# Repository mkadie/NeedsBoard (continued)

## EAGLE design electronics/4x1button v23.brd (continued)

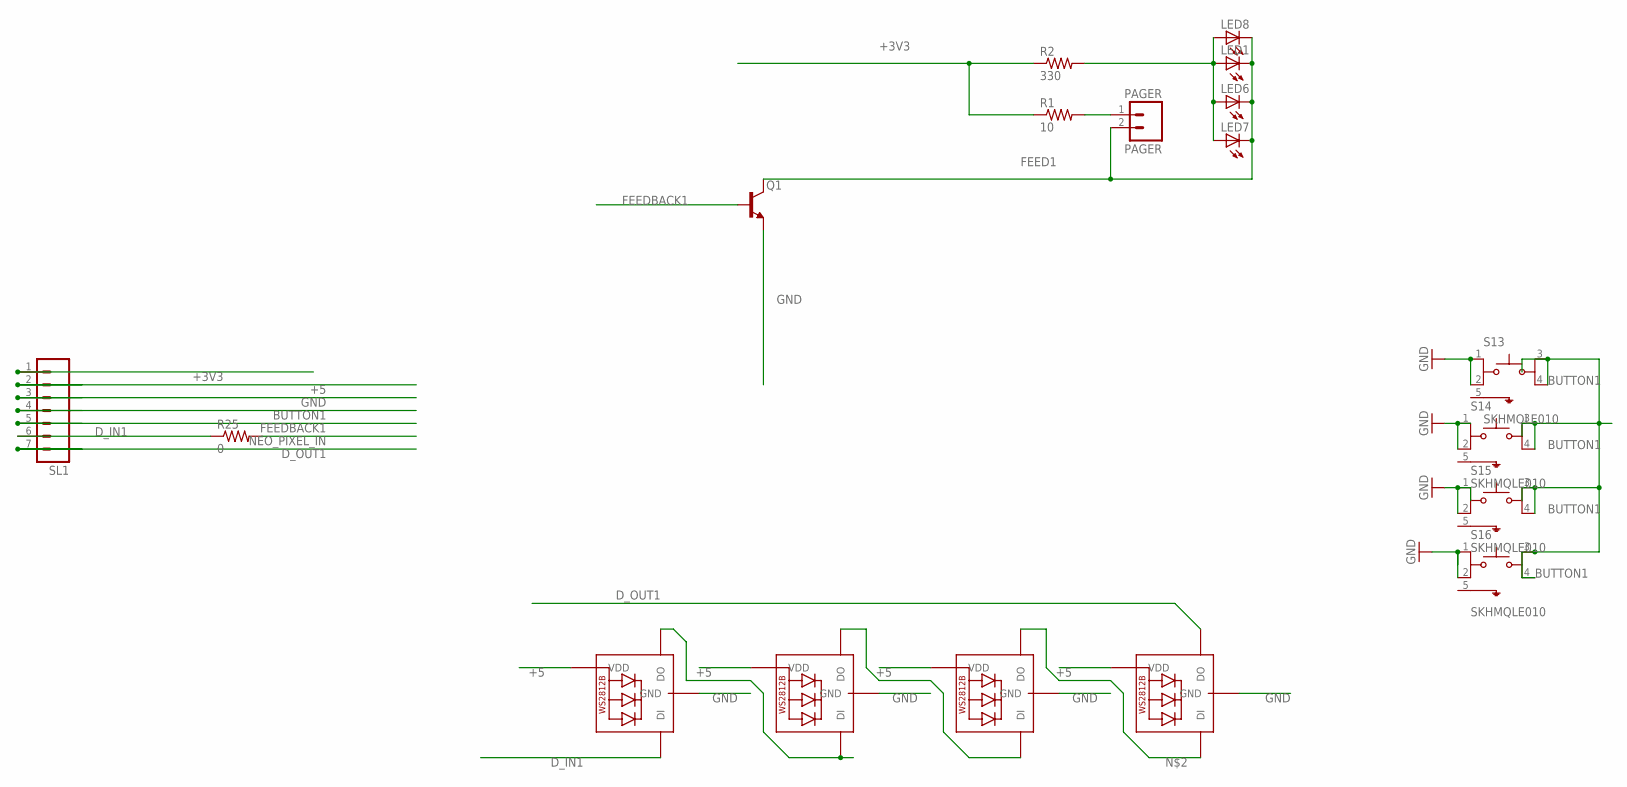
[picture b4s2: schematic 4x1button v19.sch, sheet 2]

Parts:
LED1, LED6, LED7, LED8: LEDCHIP-LED0805; CHIP-LED0805
LED2, LED3, LED4, LED5: WS2812B-V5/W; WS2812B
PAGER: PAGER; 02PA
Q1: MMUN2216; SOT95P237X112-3N
R1: 10; R0805
R2: 330; R0805
R25: 0; R0805
S13, S14, S15, S16: SKHMQLE010; SW_SKHMQLE010
SL1: MA07; 07PA

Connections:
5: S13.5, S14.5, S15.5, S16.5; also elsewhere on the board
+3V3: R1.1, R2.1, SL1.1; also elsewhere on the board
+5: LED2.1-VDD (VDD), LED3.1-VDD (VDD), LED4.1-VDD (VDD), LED5.1-VDD (VDD), SL1.2; also elsewhere on the board
BUTTON1: S13.3, S13.4, S14.3, S14.4, S15.3, S15.4, S16.3, S16.4, SL1.4; also elsewhere on the board
D_IN1: LED2.4-DIN (DI), R25.1, SL1.6
D_OUT1: LED5.2-DOUT (DO), SL1.7; also elsewhere on the board
FEED1: LED1.C, LED6.C, LED7.C, LED8.C, PAGER.2, Q1.3 (C)
FEEDBACK1: Q1.1 (B), SL1.5; also elsewhere on the board
GND: LED2.3-GND (GND), LED3.3-GND (GND), LED4.3-GND (GND), LED5.3-GND (GND), Q1.2 (E), S13.1, S13.2, S14.1, S14.2, S15.1, S15.2, S16.1, S16.2, SL1.3; also elsewhere on the board
unnamed: PAGER.1, R1.2
unnamed: LED4.2-DOUT (DO), LED5.4-DIN (DI)
unnamed: LED1.A, LED6.A, LED7.A, LED8.A, R2.2
unnamed: LED2.2-DOUT (DO), LED3.4-DIN (DI)
unnamed: LED3.2-DOUT (DO), LED4.4-DIN (DI)
NEO_PIXEL_IN: R25.2; also elsewhere on the board

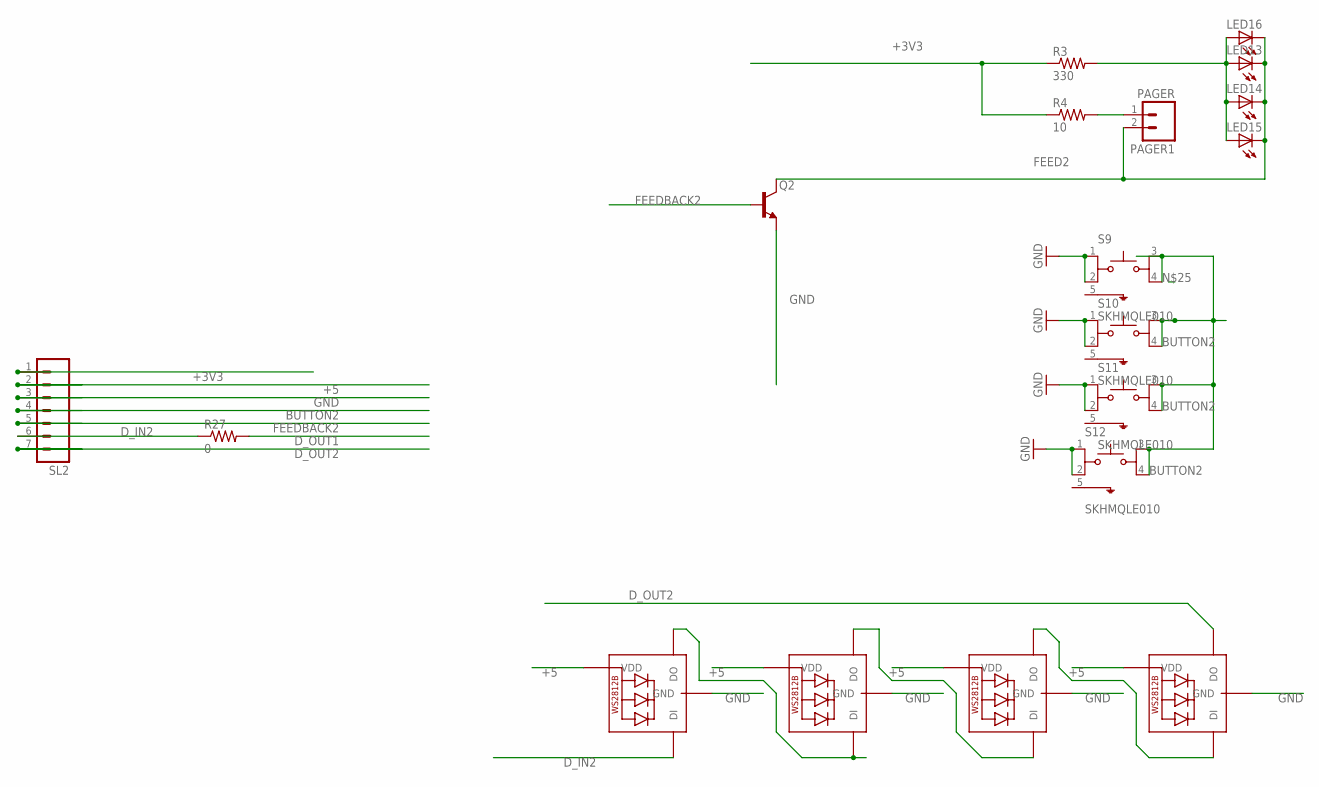
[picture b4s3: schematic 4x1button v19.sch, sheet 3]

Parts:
LED9, LED10, LED11, LED12: WS2812B-V5/W; WS2812B
LED13, LED14, LED15, LED16: LEDCHIP-LED0805; CHIP-LED0805
PAGER1: PAGER; 02PA
Q2: MMUN2216; SOT95P237X112-3N
R3: 330; R0805
R4: 10; R0805
R27: 0; R0805
S9, S10, S11, S12: SKHMQLE010; SW_SKHMQLE010
SL2: MA07; 07PA

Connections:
5: S9.5, S10.5, S11.5, S12.5; also elsewhere on the board
+3V3: R3.1, R4.1, SL2.1; also elsewhere on the board
+5: LED9.1-VDD (VDD), LED10.1-VDD (VDD), LED11.1-VDD (VDD), LED12.1-VDD (VDD), SL2.2; also elsewhere on the board
BUTTON2: S9.3, S9.4, S10.3, S10.4, S11.3, S11.4, S12.3, S12.4, SL2.4; also elsewhere on the board
D_IN2: LED9.4-DIN (DI), R27.1, SL2.6
D_OUT1: R27.2; also elsewhere on the board
D_OUT2: LED12.2-DOUT (DO), SL2.7; also elsewhere on the board
FEED2: LED13.C, LED14.C, LED15.C, LED16.C, PAGER1.2, Q2.3 (C)
FEEDBACK2: Q2.1 (B), SL2.5; also elsewhere on the board
GND: LED9.3-GND (GND), LED10.3-GND (GND), LED11.3-GND (GND), LED12.3-GND (GND), Q2.2 (E), S9.1, S9.2, S10.1, S10.2, S11.1, S11.2, S12.1, S12.2, SL2.3; also elsewhere on the board
unnamed: LED9.2-DOUT (DO), LED10.4-DIN (DI)
unnamed: LED10.2-DOUT (DO), LED11.4-DIN (DI)
unnamed: LED13.A, LED14.A, LED15.A, LED16.A, R3.2
unnamed: PAGER1.1, R4.2
unnamed: LED11.2-DOUT (DO), LED12.4-DIN (DI)

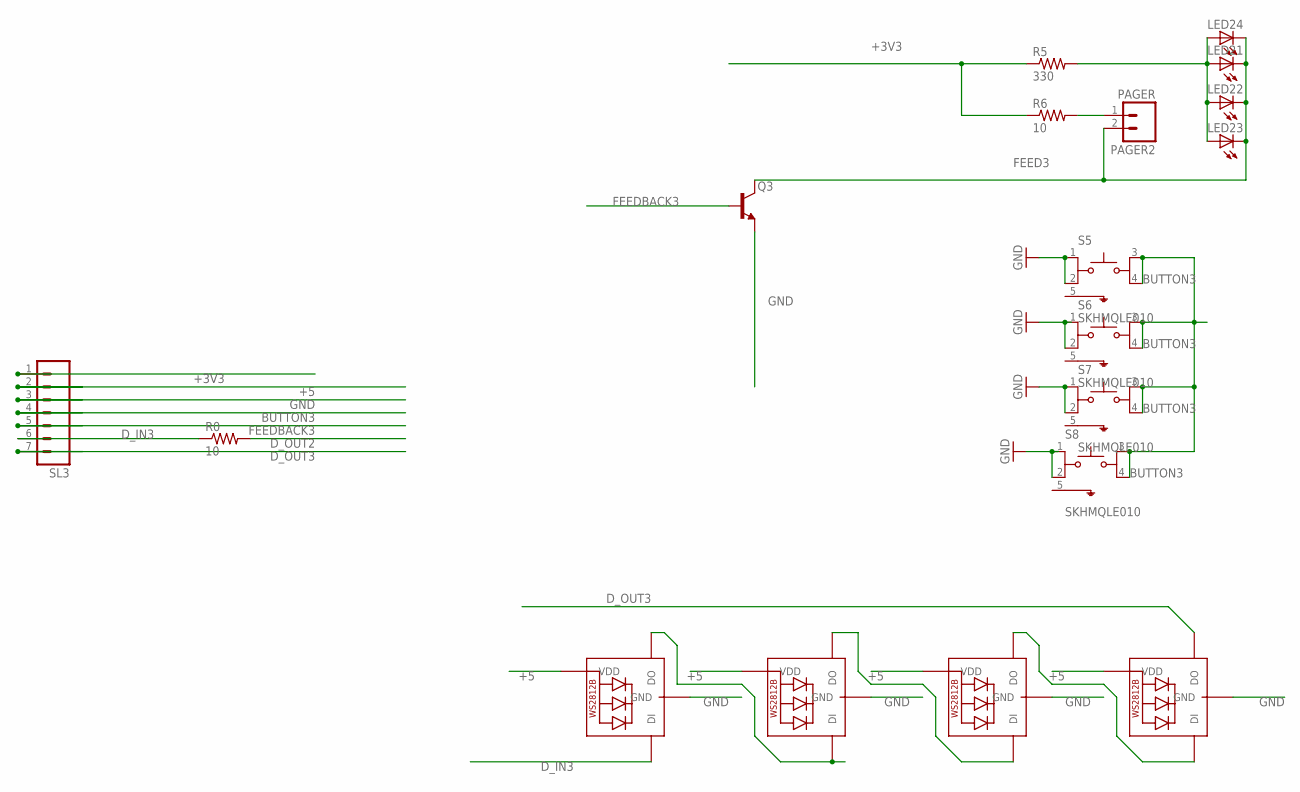
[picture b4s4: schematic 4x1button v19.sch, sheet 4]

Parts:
LED17, LED18, LED19, LED20: WS2812B-V5/W; WS2812B
LED21, LED22, LED23, LED24: LEDCHIP-LED0805; CHIP-LED0805
PAGER2: PAGER; 02PA
Q3: MMUN2216; SOT95P237X112-3N
R0, R6: 10; R0805
R5: 330; R0805
S5, S6, S7, S8: SKHMQLE010; SW_SKHMQLE010
SL3: MA07; 07PA

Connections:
5: S5.5, S6.5, S7.5, S8.5; also elsewhere on the board
+3V3: R5.1, R6.1, SL3.1; also elsewhere on the board
+5: LED17.1-VDD (VDD), LED18.1-VDD (VDD), LED19.1-VDD (VDD), LED20.1-VDD (VDD), SL3.2; also elsewhere on the board
BUTTON3: S5.3, S5.4, S6.3, S6.4, S7.3, S7.4, S8.3, S8.4, SL3.4; also elsewhere on the board
D_IN3: LED17.4-DIN (DI), R0.1, SL3.6
D_OUT2: R0.2; also elsewhere on the board
D_OUT3: LED20.2-DOUT (DO), SL3.7; also elsewhere on the board
FEED3: LED21.C, LED22.C, LED23.C, LED24.C, PAGER2.2, Q3.3 (C)
FEEDBACK3: Q3.1 (B), SL3.5; also elsewhere on the board
GND: LED17.3-GND (GND), LED18.3-GND (GND), LED19.3-GND (GND), LED20.3-GND (GND), Q3.2 (E), S5.1, S5.2, S6.1, S6.2, S7.1, S7.2, S8.1, S8.2, SL3.3; also elsewhere on the board
unnamed: LED17.2-DOUT (DO), LED18.4-DIN (DI)
unnamed: LED18.2-DOUT (DO), LED19.4-DIN (DI)
unnamed: LED21.A, LED22.A, LED23.A, LED24.A, R5.2
unnamed: PAGER2.1, R6.2
unnamed: LED19.2-DOUT (DO), LED20.4-DIN (DI)

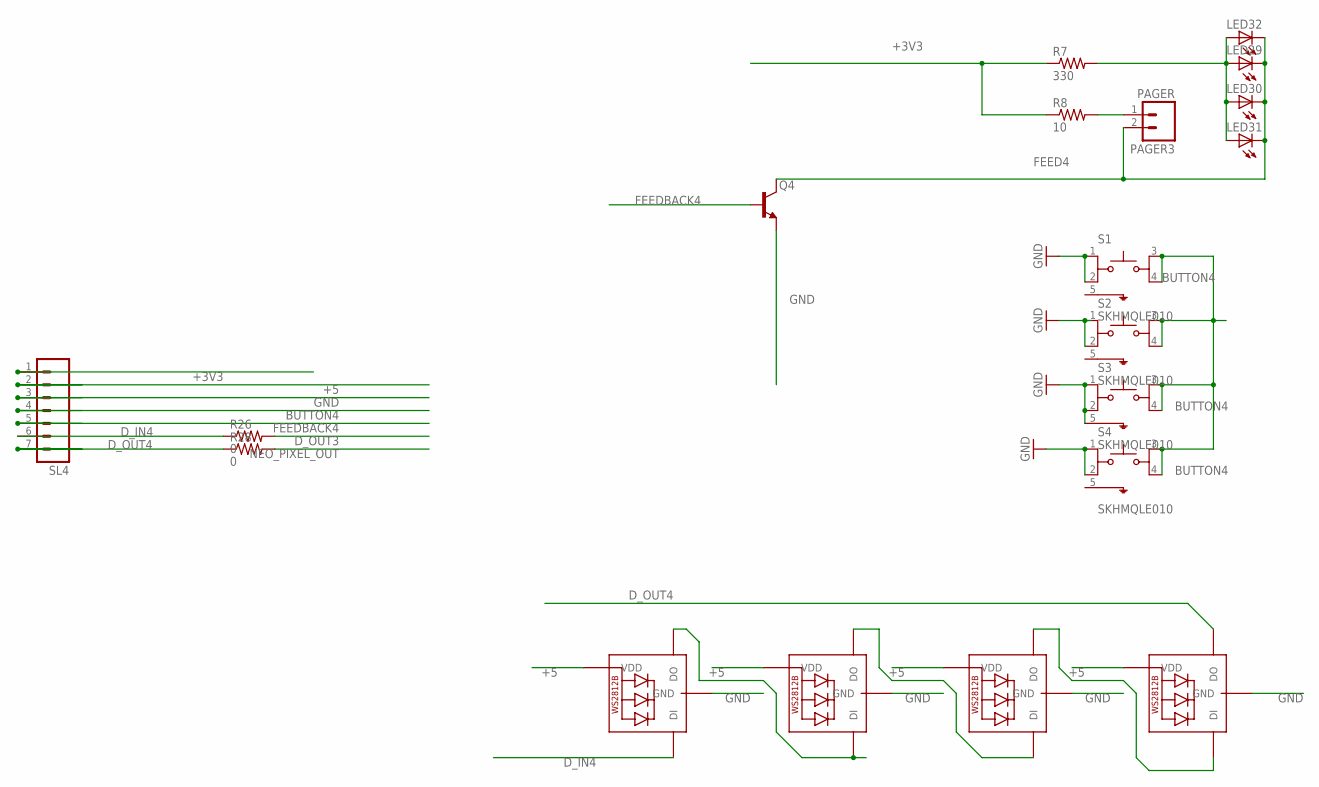
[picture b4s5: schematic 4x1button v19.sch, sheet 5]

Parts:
LED25, LED26, LED27, LED28: WS2812B-V5/W; WS2812B
LED29, LED30, LED31, LED32: LEDCHIP-LED0805; CHIP-LED0805
PAGER3: PAGER; 02PA
Q4: MMUN2216; SOT95P237X112-3N
R7: 330; R0805
R8: 10; R0805
R26, R28: 0; R0805
S1, S2, S3, S4: SKHMQLE010; SW_SKHMQLE010
SL4: MA07; 07PA

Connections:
5: S1.5, S2.5, S4.5; also elsewhere on the board
+3V3: R7.1, R8.1, SL4.1; also elsewhere on the board
+5: LED25.1-VDD (VDD), LED26.1-VDD (VDD), LED27.1-VDD (VDD), LED28.1-VDD (VDD), SL4.2; also elsewhere on the board
BUTTON4: S1.3, S1.4, S2.3, S2.4, S3.3, S3.4, S4.3, S4.4, SL4.4; also elsewhere on the board
D_IN4: LED25.4-DIN (DI), R26.1, SL4.6
D_OUT3: R26.2; also elsewhere on the board
D_OUT4: LED28.2-DOUT (DO), R28.1, SL4.7
FEED4: LED29.C, LED30.C, LED31.C, LED32.C, PAGER3.2, Q4.3 (C)
FEEDBACK4: Q4.1 (B), SL4.5; also elsewhere on the board
GND: LED25.3-GND (GND), LED26.3-GND (GND), LED27.3-GND (GND), LED28.3-GND (GND), Q4.2 (E), S1.1, S1.2, S2.1, S2.2, S3.1, S3.2, S3.5, S4.1, S4.2, SL4.3; also elsewhere on the board
unnamed: LED25.2-DOUT (DO), LED26.4-DIN (DI)
unnamed: LED26.2-DOUT (DO), LED27.4-DIN (DI)
unnamed: LED29.A, LED30.A, LED31.A, LED32.A, R7.2
unnamed: PAGER3.1, R8.2
unnamed: LED27.2-DOUT (DO), LED28.4-DIN (DI)
NEO_PIXEL_OUT: R28.2; also elsewhere on the board

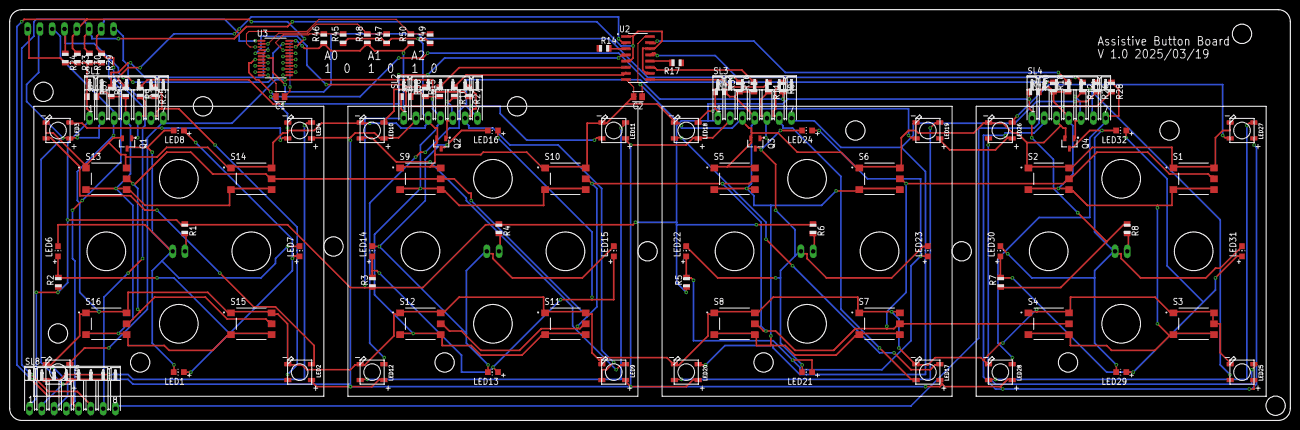
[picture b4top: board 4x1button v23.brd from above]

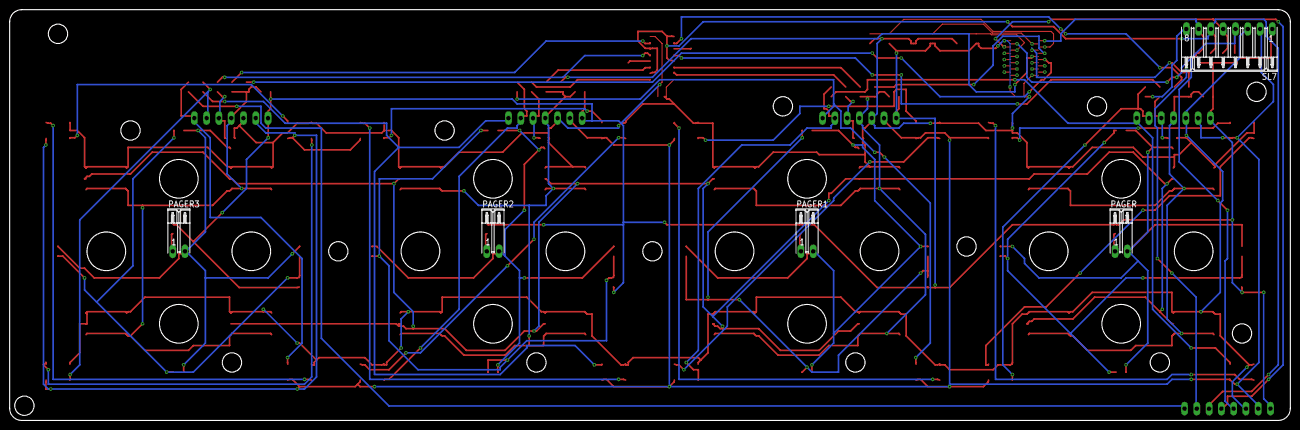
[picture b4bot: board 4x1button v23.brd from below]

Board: 2 copper layers, 265.0 x 85.0 mm, 107 parts (5 on the bottom side), 67 nets.

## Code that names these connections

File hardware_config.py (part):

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        "display_rotation": 180,
        "display_inverted": True,  # IPS panel needs INVON (0x21)
        "background_image": "/needs_small.bmp",
        "lcd_cs": "GPIO10",
        "lcd_dc": "GPIO46",
        "lcd_sclk": "GPIO12",
        "lcd_mosi": "GPIO11",
        "lcd_miso": "GPIO13",
        "lcd_backlight": "GPIO45",
        "lcd_reset": None,

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        "sound_system": "ES8311",
        "codec_sample_rate": 22050,
        "volume": 80,
        "i2s_bclk": "GPIO5",
        "i2s_ws": "GPIO7",
        "i2s_dout": "GPIO8",
        "i2s_mclk": "GPIO4",
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        "touch_screen": True,
        "touch_type": "FT6336G",
        "touch_rst": "GPIO18",
        "touch_int": "GPIO17",
        "touch_swap_xy": True,
        "touch_flip_x": True,
        "touch_flip_y": False,
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        # sleep_mode: "light" (fast wake, program resumes) or
        #             "deep" (lowest power, full restart on wake)
        # sleep_wake_pins: list of pin names that wake the device
        #   - touch_int pin wakes on screen touch
        #   - wake_button_pin wakes on boot button press
        "sleep_enabled": True,
        "sleep_timeout": 120,
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        # the board differs in three ways that all force config changes:
        #
        #   1. The auxiliary 3V3 rail (screen + other optional devices) is
        #      gated by an ACTIVE-LOW-enable load switch on GPIO10 (=board.D10)
        #      with an external pull-up (new board rev): drive D10 LOW to enable
        #      the rail, RELEASE D10 to high-Z to disable it (the pull-up floats
        #      the enable off). Same polarity as FRUITJAM_V2's active-low
        #      FULL_POWER (on A4); only the pin differs. (An earlier rev of this
        #      board used an active-HIGH TPS22917 here; the design inverted it.)
        #   2. That steals D10, which FRUITJAM_V2 uses as the encoder button.
        #      The clone's encoder button is instead wired to BUTTON1 (= GPIO0,
        #      verified on the bench 2026-09-18). Peripherals() claims BUTTON1
        #      as one of its three buttons, but machine._init_fruitjam_
        #      peripherals() deinits those right after init, so InputManager
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        "direct_buttons_active_low": True,
        "seesaw_buttons": False,

        # Rotary encoder — A/B as on FRUITJAM_V2; button on BUTTON1/GPIO0
        # rather than V2's D10, which this board uses for the rail (note 2).
        "rotary_encoder": True,
        "encoder_navigation": True,
        "encoder_pin_a": "D8",
        "encoder_pin_b": "D9",
        "encoder_button_pin": "BUTTON1",   # = GPIO0 (see note 2)
        "encoder_button_index": 0,

        "wake_button_pin": None,
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        "debounce_time": 0.05,

        # Emergency push/hold — live now that audio works and the encoder
        # button resolves to BUTTON1. Both route through encoder_button_pin.
        "emergency_push_enabled": True,
        "emergency_push_sound": "/button_sounds/emergency.mp3",
        "emergency_hold_enabled": True,
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        # Active-LOW with internal pull-up. max_buttons here counts decoder-bus
        # buttons (none here); the 3 onboard ones are direct GPIO.
        "max_buttons": 0,
        "direct_button_pins": ["BUTTON1", "BUTTON2", "BUTTON3"],
        "direct_buttons_active_low": True,

        # Rotary encoder — not used in this variant (keyboard handles navigation)
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        "encoder_button_pin": None,
        "encoder_button_index": 0,

        # BUTTON1 is already claimed by direct_button_pins above; leaving a
        # wake_button_pin here too would double-claim the pin and crash
        # InputManager init. Onboard buttons handle wake via the grid.
        "wake_button_pin": None,
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        "usb_host_dm": "USB_HOST_DATA_MINUS",
        "usb_host_5v_power": "USB_HOST_5V_POWER",

        # Direct buttons OFF — BUTTON1/BUTTON2/BUTTON3 GPIOs are repurposed
        # as the rotary encoder. Same physical hardware, different reading
        # mode: BUTTON1 = encoder A, BUTTON2 = encoder B, BUTTON3 = click.
        "max_buttons": 0,
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        # (we want it to open the language picker instead).
        "rotary_encoder": True,
        "encoder_navigation": False,
        "encoder_pin_a": "BUTTON1",
        "encoder_pin_b": "BUTTON2",
        "encoder_button_pin": "BUTTON3",
        "encoder_button_index": 0,

        "wake_button_pin": None,
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
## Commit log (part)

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2025-04-30 Initial File round up and checkin on project
2025-05-16 Testing Link to Github and publish code
2025-05-16 Release Canidate code checkin 1
2025-05-16 Version 1.2 Release Canidate 2 Missing files for release canidate and code.py was in a hardware test mode loop before. Both Fixed
2025-05-30 Updates to model Files and inclution of utility file
2025-06-13 update utilities and test slide show
2025-06-14 help wanted
2026-03-28 Revert "Improve CYD_PLUS sleep: display SLPIN + MCLK off"
    This reverts commit efd8feb9aa5bc307afdd859ba34b449d05296963.
2026-05-17 Consolidated V3 Compute Module
    Massive info dump corelated with AI and review, little long winded, for the v3 compute module for T-Rex Talker
2026-05-30 My doctorial intent
    Person vision of how this work might be used for getting my doctorate degree.
2026-06-01 Create readme.md
    this directory has been giving me problems so placeholder
2026-06-01 importing old gdocs as .md files
2026-06-13 Add funding to support work
2026-06-14 Add Patreon funding source
    Updated funding sources to include Patreon link.
